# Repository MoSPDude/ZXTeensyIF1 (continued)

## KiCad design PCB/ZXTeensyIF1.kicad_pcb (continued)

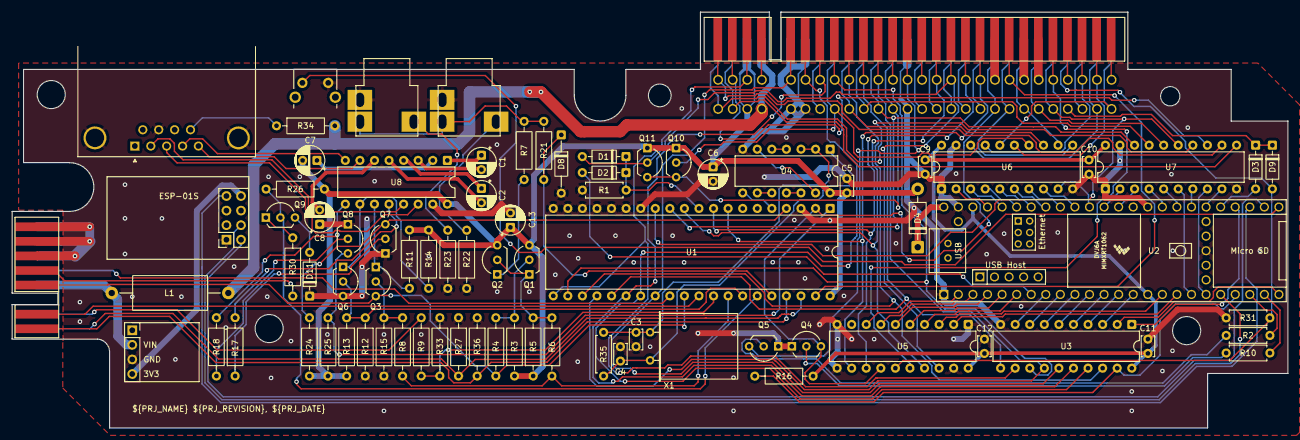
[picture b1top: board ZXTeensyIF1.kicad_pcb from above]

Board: 2 copper layers, 222.4 x 72.5 mm, 81 parts (0 on the bottom side), 148 nets.

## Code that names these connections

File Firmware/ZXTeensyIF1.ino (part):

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const uint8_t RESET_PIN = 31;
const uint8_t RESET_IN_PIN = 2;
const uint8_t BUTTON_PIN = 33;
const uint8_t ROMCS_PIN = 35;
const uint8_t ROMCS_IN_PIN = 3;
const uint8_t IF1_DIS_PIN = 5;
const uint8_t NMI_PIN = 30;
const uint8_t RD_PIN = 1;
const uint8_t WR_PIN = 0;
const uint8_t MREQ_PIN = 24;
const uint8_t IOREQ_PIN = 25;
const uint8_t M1_PIN = 4;
const uint8_t NC_IN_A_PIN = 28;
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const uint8_t NC_IN_C_PIN = 37;

const uint8_t INPUT_PINS[] = {
    RESET_IN_PIN, MREQ_PIN, RD_PIN, IOREQ_PIN, WR_PIN, M1_PIN, ROMCS_IN_PIN,
    19, 18, 14, 15, 40, 41, 17, 16, 22, 23, 20, 21, 38, 39, 26, 27, // Address bus
    BUTTON_PIN, NC_IN_A_PIN, NC_IN_B_PIN, NC_IN_C_PIN
};
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const uint32_t DATA_OUT_PIN_BITMASK = CORE_PIN34_BITMASK;

const uint8_t OUTPUT_PINS[] = {
    LED_PIN, ROMCS_PIN, NMI_PIN, IF1_DIS_PIN
};

const uint8_t SD_CS_PIN = 46;
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        case STATE_RESET :
            resetState = RESET_ACTIVE;
            digitalWriteFast(RESET_PIN, 1);
            digitalWriteFast(ROMCS_PIN, 1);
            disableData();
            break;
        case STATE_ROM_ENABLE :
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        case STATE_ROM_DISABLE :
            resetState = RESET_HOLD;
            digitalWriteFast(DATA_DIS_PIN, 1);
            digitalWriteFast(ROMCS_PIN, 0);
            digitalWriteFast(RESET_PIN, 0);
            break;
    }
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            // Page in the soft ROM
            if (page_now_)
            {
                digitalWriteFast(ROMCS_PIN, 1);
                romEnabled = true;
            } else {
                romCsEnable = true;
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        // Fall back to real ROM
        if (page_now_)
        {
            digitalWriteFast(ROMCS_PIN, 0);
            romEnabled = false;
        } else {
            romCsDisable = true;
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    zxC2BankPtr = 0x00;
    romEnabled = false;
    romSelected = BANK_ROM0;
    digitalWriteFast(ROMCS_PIN, 0);
    digitalWriteFast(IF1_DIS_PIN, 0);
    digitalWriteFast(NMI_PIN, 0);
    delay(100);

    // Load the built-in Interface 1 soft ROM
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        !digitalReadFast(BUTTON_PIN))
    {
        nmiPending = true;
        digitalWriteFast(NMI_PIN, 1);
    }
}

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            busRdActive = false;
            if (romCsEnable)
            {
                digitalWriteFast(ROMCS_PIN, 1);
                romEnabled = true;
                romCsEnable = false;
                if (isDivMmcSelected())
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                }
            } else if (romCsDisable)
            {
                digitalWriteFast(ROMCS_PIN, 0);
                romEnabled = false;
                romCsDisable = false;
                if (isDivMmcSelected())
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                            }

                            nmiPending = false;
                            digitalWriteFast(NMI_PIN, 0);
                        }
                    } else if (divMmcPresent && !mf128Paged)
                    {
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
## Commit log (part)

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2026-01-24 feat: First upload
2026-01-24 feat: Initial PCB upload
2026-01-24 feat: Upload initial PCB v0.3
2026-01-24 feat: Add current status
2026-01-24 fix: missed KiCad library credit
2026-01-24 fix: Minor tweak
2026-01-24 fix: Typos
2026-01-26 Fix Arduino folder name
2026-01-26 feat: update ROM menu for 13 pages
2026-01-26 feat: introduce ROM menu
2026-01-26 feat: Introduce menu ROM
2026-01-26 fix: Update README for Menu ROM
2026-01-26 Update README with SD card info
2026-01-27 Store Teensy pin assignment spreadsheet
2026-01-27 fix: Menu clear first 16K RAM
2026-01-27 feat: Tidy code, and debounce NMI button
2026-01-28 Preserve DivMMC RAM on reset
2026-01-28 Update menu
2026-01-28 Update configuration
2026-01-29 Move more memory into RAM2
2026-01-29 fix: Reset with DivMMC active did not detect SD card again
2026-01-29 fix: Attempt to improve stability
2026-01-30 Minor tweaks
2026-01-30 feat: Add firmware update from SD card
2026-01-30 feat: Add boot into menu option
2026-01-31 fix: External ROMs use soft ROM too
2026-01-31 Document 128K GAL modification for +3 soft ROMs
2026-01-31 Make ZXC2 ROMs temporary, and see Spectrum soft ROMs
2026-02-01 Lock ZXC2 paging when loading IF2 ROMs
2026-02-01 fix: Spectrum ROMs reload after ZXC2 ROMs
2026-02-02 fix: Initialise menu on reload
2026-02-02 Add version string, and IF2 icon
2026-02-05 feat: Add ESP-01S header to PCB v0.5
2026-02-05 feat: Introduce hardware Serial8 as MB03+ UART
2026-02-06 Refactor SPI and UART drivers
2026-02-06 Add UART to menu
2026-02-07 feat: Reimplement parts of HardwareSerialIMXRT into UartZXTeensy
2026-02-08 Add silkscreen text
2026-02-08 fix: ZXC2 banking on nWR
2026-02-08 Disable interrupts on FW update
2026-02-09 Enable microdrive in MF128 with DivMMC
2026-02-09 Return to menu after ZXC2 ROM
2026-02-11 Add Kempston USB mouse
2026-02-12 Introduce RTC module
2026-02-12 feat: add RTC time set
2026-02-12 Update RTC on register 0xD access
2026-02-13 Put spectrum into reset as early as possible
2026-02-22 Try to startup faster
2026-02-22 Use active DTR and TXDATA from MAX232
2026-02-22 fix: Minor PCB tweak
2026-02-22 Blank menu whilst loading
2026-02-24 feat: Bridge DivMMC SPI to SDHC controller
2026-02-24 Update headers
2026-02-24 fix: DivMMC writes over SDHC
2026-02-25 fix: Tidy up SDHC and menu code
2026-02-25 feat: SDHC read using DMA
2026-02-25 fix: Allow warm reset of DivMMC, and fix ROMs across reset
2026-02-25 fix: Add faster SD card detect
2026-02-25 fix: NMI to DivMMC
2026-02-26 Disable DivMMC read DMA, add NMI tracing
2026-02-26 fix: DivMMC NMI crash due to RTC
2026-02-27 Add pause before redrawing menu
2026-02-27 feat: Introduce Kempston USB gamepad
2026-02-27 feat: Hold reset to hard reset
2026-02-27 Introduce file browser
2026-02-27 Remove stray directory icon from menu
2026-02-28 Introduce ROM loading from browser
2026-02-28 Add browser file type selection menu
2026-02-28 feat: Add z80 loading from ZXPicoIF2Lite
2026-02-28 Reclaim 8KB from DivMMC ROM space
2026-02-28 Minor tweak
2026-03-02 fix: Attempt to start faster
2026-03-02 fix: menu triggering FW update on browser open
2026-03-04 feat: Add NTP time sync over WIFI
2026-03-04 feat: Add menu for WIFI NTP
2026-03-04 Use default date to detect RTC not set
2026-03-04 Add tools to menu
2026-03-06 feat: Add tape selection to menu
2026-03-06 Add missing menu icons
2026-03-06 fix: Size error in ring buffer
2026-03-07 fix: Minor warning
2026-03-07 Code size optimisation - allow for -Os, with ISRs at -O3
2026-03-07 feat: Introduce tape player
2026-03-07 feat: Introduce TZX loading
2026-03-07 Double select ROMs in load ROM to restart
2026-03-08 feat: Introduce DivMMC SD images
2026-03-08 fix: Disable device, and re-enable on hard reset
2026-03-08 fix: create configuration defaults correctly
2026-03-08 feat: Move SPI to SDHC bridge, to use SdFat SdioCard
2026-03-09 feat: Add HTTP server for file access
2026-03-09 Move UART bridge back to using Serial8
2026-03-09 Introduce HTTP upload via PUT
2026-03-09 fix: RTC day off by one
2026-03-09 Create directories for new files
2026-03-09 Reduce polling frequency, and optimise loop
2026-03-09 feat: Introduce SPECTRA shadow ROM banking
2026-03-12 feat: Introduce ZXC3 flash ROM support
2026-03-12 Split ROMs into Spectrum and Foreground types
2026-03-13 fix: ROM loading after reset
2026-03-13 fix: RingBuffer canWrite truncation
2026-03-16 feat: introduce lib765, fix off by one DSK issues
2026-03-16 Add FDC DSKs to menu
2026-03-17 feat: Allow DivMMC with +3e ROMs
2026-03-18 Reduce DivMMC SD read buffer size
2026-03-18 feat: Add stored configs
2026-03-19 feat: Add Prism VTX5000 over WiFi
2026-03-19 Adjust UART buffer size
2026-03-19 fix: ESP-01S leaving transparent mode
2026-03-19 fix: UART read level indicator
2026-03-19 Attempt to balance main loop ticks vs ISR rate
2026-03-19 Add time to main menu
2026-03-20 fix: TZX loading tweaks
2026-03-20 Gather defines to one file
2026-03-20 Add CPU temperature status
2026-03-20 fix: UART after WiFi NTP
2026-03-21 feat: Add debug menu, with USB buttons
2026-03-22 feat: Introduce Centronics port
2026-03-22 feat: add ZX LPrint III emulation
2026-03-22 Add PCB v0.7 images
2026-03-23 Tidy soft ROM initialisation
2026-03-23 Remove enable check from ISRs
2026-03-23 Flatten ISR code some more
2026-03-23 Update configs, and ESXDOS ROM present
2026-03-23 Increase UART to hold 2 x MTU packets from +IPD
2026-03-23 fix: Restrict VTX5000 data rate to 1200 baud
2026-03-25 fix: snprintf warnings
2026-03-26 Revert UART status to the RingBuffer size
2026-03-26 Refactor read ISR again
2026-03-27 Add PS3 and PS4 USB controller mappings
2026-03-28 More ROM paging tweaks
2026-03-29 fix: Typo in mask
2026-04-01 Make the Spectrum band bright in Menu
2026-04-25 PCB move C6 slightly, C13 to 47uF
2026-04-25 Enable 4 buttons for gamepad
2026-05-01 fix: Increase menu redraw delay
2026-05-01 fix: LPRINT III paging
2026-05-01 Update configs
2026-05-04 feat: Move menu into ROM space
2026-05-05 feat: Introduce in-game menu
2026-05-05 Preserve menu ROM
2026-05-07 feat: Add in-game TZX and DSK swapping
2026-05-08 Document I/O ports
2026-05-09 feat: Add in-game tape browser
2026-05-09 fix: TAP file browsing
2026-05-10 Add in-game ROM and status info
2026-05-18 Minor updates, add DivMMC 512KB option
2026-05-20 feat: Add return to BASIC in menu
2026-05-21 feat: Add inteface 1 vs DivMMC toggle, improve Break into BASIC
2026-05-21 Improve in-game ROM status
2026-05-22 fix: NMI into menu from MF128
2026-05-25 fix: Split SD buffers to per device, and fix resets
2026-05-30 Enable DivMMC SD card and images concurrently
2026-06-01 fix: Improve menu stability
2026-06-06 fix: odd UART menu stability
2026-06-06 fix: Missed UART buffer clear
2026-06-09 Adjust RAM1 vs RAM2 balance
2026-06-27 feat: Introduce WebDAV class 1 support
2026-06-27 fix: Save/restore AY registers for in-game menu
2026-06-27 fix: Minor typos
2026-06-28 feat: Introduce save states
2026-06-28 fix: Fix saved state as 48K with Internal ROM
2026-06-28 fix: Save and restore more state
2026-06-30 Modify z80torom to place final loader in ROM
2026-06-30 fix: Configuration and save slot on restore
